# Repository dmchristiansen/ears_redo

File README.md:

# ears_redo
Recreation of Mutable Instruments' Ears (https://github.com/pichenettes/eurorack/tree/master/ears/hardware_design) done in KiCad.

This is redone with 0603 components instead of 0402.  KiCad's function for importing schematics from Eagle doesn't work very well for the PCB art on the front panel.
Also, I wanted to practice layout a more compact board than I've done in the past.

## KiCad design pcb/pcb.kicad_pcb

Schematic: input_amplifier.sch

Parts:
C3: 68p; C_0603
C5, C16: 4.7u; C_0603
C7: 22p; C_0603
J1, J2: PJ301M-12
MIC1: Conn_01x02; Pin_Header_Straight_1x02_Pitch2.54mm
R1, R8: 510; R_0603
R4, R6: 10k; R_0603
R5: 1.0M; R_0603
R7: 50kB; Alpha9mmPot
U1: OPA1641; OPA1641AIDGKR

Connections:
AMP_OUT: C7.2, C16.1, R7.1, U1.6; also elsewhere on the board
GND: C3.2, J1.1, J2.1, MIC1.1, R5.2, R6.2, R8.2; also elsewhere on the board
unnamed: C3.1, C5.1, J1.3
unnamed: C5.2, R4.2, R5.1
unnamed: C7.1, R6.1, R7.2, U1.2
unnamed: C16.2, R1.2
unnamed: J1.2, MIC1.2
unnamed: J2.3, R1.1
unnamed: R4.1, U1.3
unnamed: R7.3, R8.1
VCC: U1.7; also elsewhere on the board
VEE: U1.4; also elsewhere on the board

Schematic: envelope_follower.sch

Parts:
Attack1: Conn_01x03; Pin_Header_Straight_1x03_Pitch2.54mm
C8, C11: 1u; C_0603
C10: 68p; C_0603
C14: 1.0n; C_0603
C15: 4.7u; C_0603
D4, D5, D6, D7, D8: D; D_SOD-523
Decay1: Conn_01x03; Pin_Header_Straight_1x03_Pitch2.54mm
Gate1: Conn_01x03; Pin_Header_Straight_1x03_Pitch2.54mm
J3, J4: PJ301M-12
LED1, LED2, LED3: LED; LED_D3.0mm
R2, R3: 510; R_0603
R9, R18, R22, R26: 20k; R_0603
R10, R11, R24: 10k; R_0603
R12, R19, R20, R21, R23, R29, R33, R34, R35: 100k; R_0603
R13, R14, R15, R16, R17, R30, R31, R32: 200k; R_0603
R25: 2.7k; R_0603
R27: 1.0M; R_0603
R28: 430k; R_0603
U2, U3: LM324; LM324PWR

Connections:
AMP_OUT: C15.1; also elsewhere on the board
CLIP: D4.2, U2.8
ENVELOPE: R2.2, U2.6 (-), U3.1, U3.2 (-), U3.5 (+)
FULL_WAVE: C14.2, D5.2, D6.1, R30.1, U2.10 (+), U3.14
GATE: C10.2, R3.2, R14.1, U2.1, U2.12 (+)
GND: C8.2, C11.2, J3.1, J4.1, LED1.1, R9.2, R10.2, R19.2, R20.2, R21.2, R22.2, R27.1, U2.3 (+), U3.10 (+), U3.12 (+); also elsewhere on the board
unnamed: Attack1.1, R25.2
unnamed: Attack1.2, D5.1, R29.2
unnamed: Attack1.3, R26.2
unnamed: C8.1, D4.1, R11.2
unnamed: C10.1, R13.1, R14.2, R15.1, U2.2 (-)
unnamed: C11.1, R23.1, R24.1, R25.1, R26.1, R27.2, R28.1, R29.1, U3.3 (+)
unnamed: C14.1, R30.2, R31.1, R34.1, R35.1, U3.13 (-)
unnamed: C15.2, R31.2, R32.2
unnamed: D6.2, Decay1.2, R28.2
unnamed: D7.1, R32.1, R33.2, U3.9 (-)
unnamed: D7.2, D8.1, U3.8
unnamed: D8.2, R33.1, R34.2, R35.2
unnamed: Decay1.1, R23.2
unnamed: Decay1.3, R24.2
unnamed: Gate1.1, R22.1
unnamed: Gate1.2, R16.1, R17.2, R21.1, U2.5 (+)
unnamed: Gate1.3, R20.1
unnamed: J3.3, R2.1
unnamed: J4.3, R3.1
unnamed: LED1.2, R11.1
unnamed: LED2.1, R9.1, U3.6 (-)
unnamed: LED2.2, U3.7
unnamed: LED3.1, R10.1, U2.13 (-)
unnamed: LED3.2, U2.14
unnamed: R12.2, R13.2
unnamed: R18.2, R19.1, U2.9 (-)
VCC: R16.2, R18.1; also elsewhere on the board
VEE: R12.1; also elsewhere on the board
~GATE: R15.2, R17.1, U2.7

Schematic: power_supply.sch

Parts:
C1, C2: 22u; C_1206
C4, C6, C9, C12, C13: 100n; C_0603
D1, D2: D_Schottky; D_SOD-523
JP4: Conn_02x05_Odd_Even; Pin_Header_Straight_2x05_Pitch2.54mm
L1, L2: L_Core_Ferrite; L_0603
U2, U3: LM324; LM324PWR

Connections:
GND: C1.2, C2.1, C4.2, C6.1, C9.2, C12.1, C13.2, JP4.3, JP4.4, JP4.5, JP4.6, JP4.7, JP4.8, U2.11 (V-); also elsewhere on the board
unnamed: D1.1, L1.1
unnamed: D1.2, JP4.1, JP4.2
unnamed: D2.1, JP4.9, JP4.10
unnamed: D2.2, L2.1
VCC: C1.1, C4.1, C9.1, C13.1, L1.2, U2.4 (V+), U3.4 (V+); also elsewhere on the board
VEE: C2.2, C6.2, C12.2, L2.2, U3.11 (V-); also elsewhere on the board

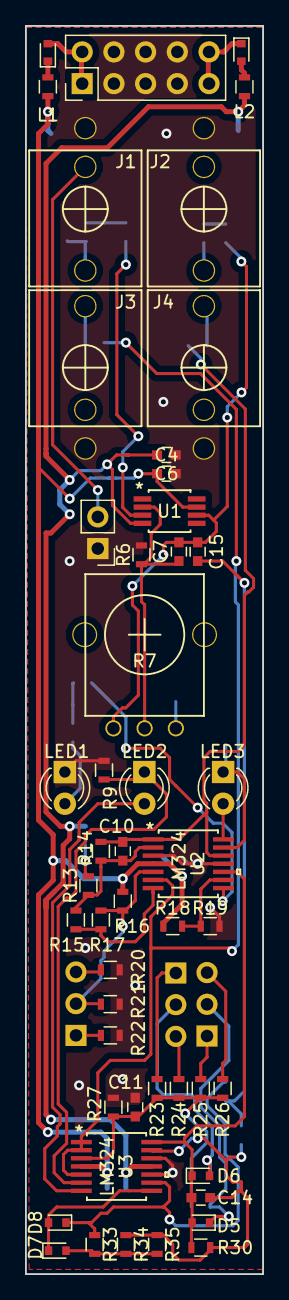
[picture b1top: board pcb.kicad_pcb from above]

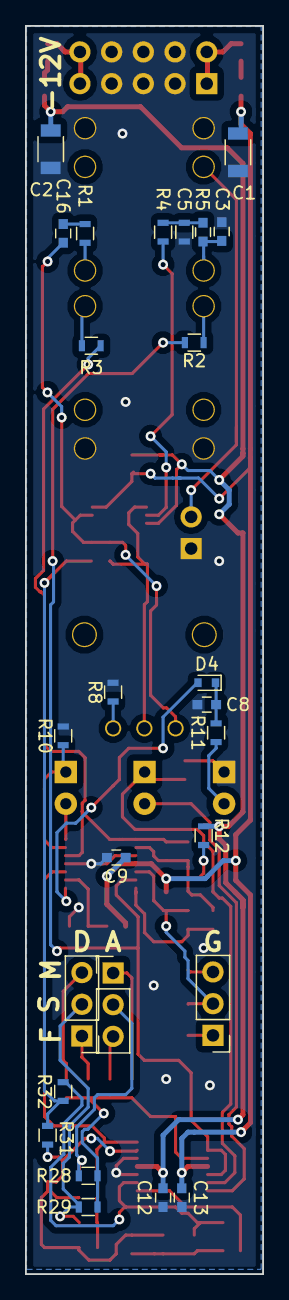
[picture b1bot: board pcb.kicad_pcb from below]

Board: 2 copper layers, 19.0 x 100.0 mm, 75 parts (26 on the bottom side), 47 nets.

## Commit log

2019-01-09 tidied folders

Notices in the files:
parts and their libraries:
Copyright 2016 Accelerated Designs. All rights reserved.
